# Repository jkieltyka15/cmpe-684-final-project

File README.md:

# Smart Wireless Sensor Network (WSN) Parking Lot
## Overview
This repository is a collection of research, hardware implementations and software implementations for a smart parking lot that displays the vacancy status of each parking space. The scope of the project was limitted to ten spaces and is meant to be a proof of concept to satisfy the final project requirement for CMPE-684: Wireless Sensor Networks at the University of Maryland, Baltimore County.

## Hardware
All PCB design files were created using KiCad and all stl files for 3D prints were developed using Autodesk TinyCAD. The filament used for the 3D prints is PLA.

For electronics, the project truly revolves around the Arduino Nano. All of the sensor nodes and the base station utilize this microcontroller. Time of Flight (ToF) sensors are used to detect if a vehicle is present and the NRF24L01 radio is used for network communication between sensor nodes and the base station.

The output of the base station is composite video with a limitted display resolution. However, the final resolution seems to scale well with most display scalers.

## Software
The Arduino IDE was used for the research examples. However, PlatformIO was used for the actual implementation since it offered superior project structure and organization.

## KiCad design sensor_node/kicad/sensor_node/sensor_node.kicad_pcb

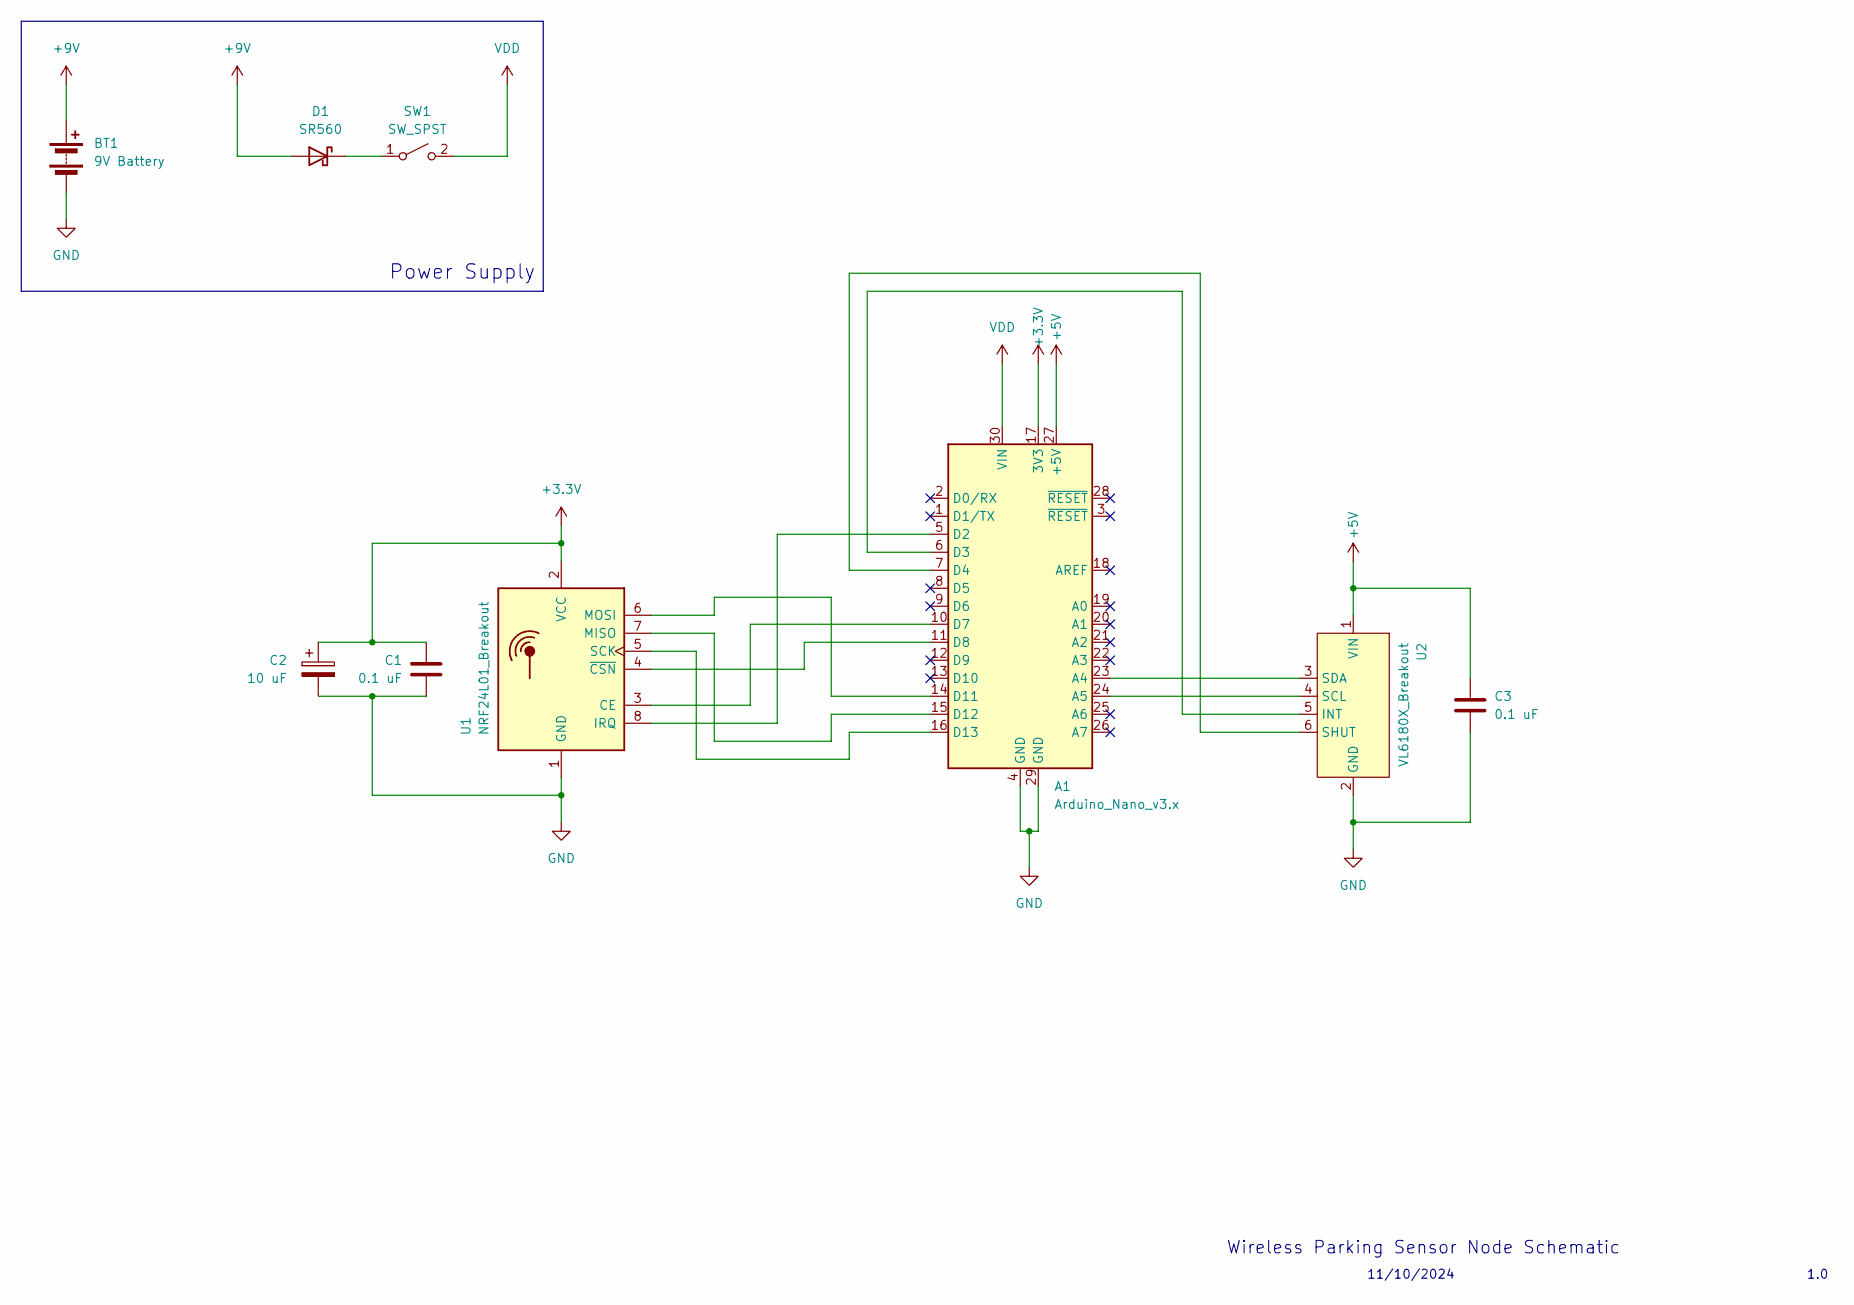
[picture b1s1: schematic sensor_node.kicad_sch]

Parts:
A1: Arduino_Nano_v3.x; Arduino_Nano
BT1: 9V Battery; PinHeader_1x02_P2.54mm_Vertical
C1, C3: 0.1 uF; C_Disc_D5.1mm_W3.2mm_P5.00mm
C2: 10 uF; CP_Radial_D5.0mm_P2.50mm
D1: SR560; D_DO-201AD_P15.24mm_Horizontal
SW1: SW_SPST; PinHeader_1x02_P2.54mm_Vertical
U1: NRF24L01_Breakout; nRF24L01_Breakout
U2: VL6180X_Breakout

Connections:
+3.3V: A1.17 (3V3), C1.1, C2.1, U1.2 (VCC)
+5V: A1.27 (+5V), C3.1, U2.1 (VIN)
+9V: BT1.1 (+), D1.2 (A)
GND: A1.4 (GND), A1.29 (GND), BT1.2 (-), C1.2, C2.2, C3.2, U1.1 (GND), U2.2 (GND)
unnamed: A1.23 (A4), U2.3 (SDA)
unnamed: A1.24 (A5), U2.4 (SCL)
unnamed: A1.5 (D2), U1.8 (IRQ)
unnamed: A1.6 (D3), U2.5 (INT)
unnamed: A1.7 (D4), U2.6 (SHUT)
unnamed: A1.10 (D7), U1.3 (CE)
unnamed: A1.11 (D8), U1.4 (~CSN)
unnamed: A1.14 (D11), U1.6 (MOSI)
unnamed: A1.15 (D12), U1.7 (MISO)
unnamed: A1.16 (D13), U1.5 (SCK)
unnamed: D1.1 (K), SW1.1 (A)
VDD: A1.30 (VIN), SW1.2 (B)

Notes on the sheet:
11/10/2024
1.0
Wireless Parking Sensor Node Schematic
Power Supply

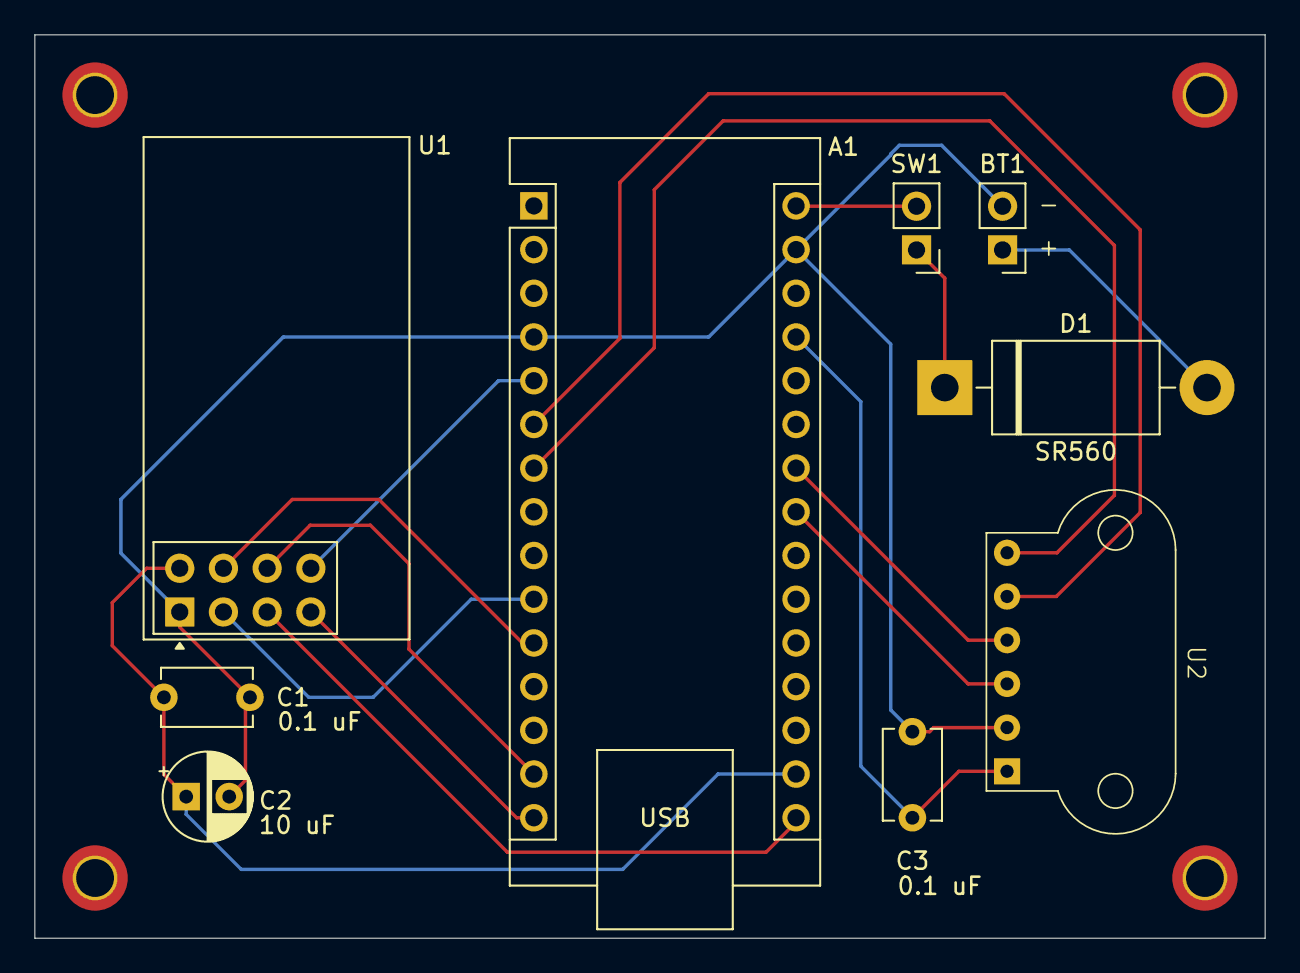
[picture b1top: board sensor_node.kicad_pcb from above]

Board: 2 copper layers, 71.5 x 52.5 mm, 13 parts (0 on the bottom side), 16 nets.

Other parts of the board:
MH1, MH2, MH3, MH4: MountingHole_2.2mm_M2_DIN965_Pad_TopBottom

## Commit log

2024-11-10 Added a transmitter and receiver demo to confirm functionality of the nRF24L01 module with Arduino Nanos.
2024-11-12 Added a demo for the nRF24L01 to confirm functionality with an Arduino Nano.
2024-11-12 Updated CE pins for RX and TX for the nRF24L01 demo.
2024-12-01 Added KiCad project files for the base station and sensor node. Added stl for base station's 3d printed enclosure. Added .gitignore.
2024-12-06 Added stl files for the sensor node enclosure and number tags.
2024-12-14 Added PlatformIO project for the sensor node. Began implementing SensorNode class. Implemented parking space detection for sensor node.
2024-12-15 Implemented transmitting and forwarding update messages. Currently received message data is not what is expected.
2024-12-15 Resolved issue with messages not being sent and received correctly. Added auto ACK and dynamic payload size.
2024-12-15 Added ingress routing to base station for sensor nodes via a parking map algorithm.
2024-12-15 Fixed grammar in logs.
2024-12-15 Added simple base station code. Base station can receive messages but does nothing with them.
2024-12-16 Base station now saves reported statuses of sensor nodes.
2024-12-16 Base station now shows the number of available spaces on a display.
2024-12-17 Fixed auto ack feature. Added persistent message attempts when messages fail to be delivered.
2024-12-17 Removed persistent messaging. Causes network traffic jams.
2024-12-17 Sensor nodes wait for channel to not have traffic before sending a message.
2024-12-17 Added heartbeating and variable loop delay to avoid collision.
2024-12-18 Upgraded base station GUI to show map of parking lot and draw cars in occupied parking spaces.
2024-12-18 Tweaked min and max values for looping. Added timeout for waiting for channel to be open.
2024-12-18 Update readme file to be more descriptive.
2024-12-18 Resolved grammar errors in readme file.
